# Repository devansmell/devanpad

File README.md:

# devanpad
devanpad is a 4 key macropad with an OLED Display, and QMK firmware.

It serves as an example piece/reference for the hackpad YSWS, since it contains an implementation of every common part.

## Features:
- Open faced ~~sandwich~~ PCB board design.
- OLED Date and Time / Customisable text through python!
- 4 Keys for whatever you want!

## CAD Model:
I quite like the aesthetics of an open PCB, makes me feel like a bond villian; so I am only making a base for the circuit board to sit into. Everything is held together by 4 screws going into the base through the PCB.

Modeled in OnShape.

## PCB
Here's my PCB! It was made in KiCad. The silkscreen is a collection of inside jokes and random images from my computer.

Schematic

PCB

I used Cherry MX1's for the keyswitch footprints. My routing is god awful but if it aint broke dont fix it !!!!

## Firmware Overview

Originally I planned to use QMK firmware, but I switched to CircuitPython + KMK because it made OLED control and development significantly easier.

The firmware:
- Reads key inputs via KMK
- Drives OLED display in real time
- Receives time/date from a Python script over USB serial
- Cycles display modes using a keypress

---

## Host Software (PC Time Sync)

The keyboard receives live system time and date from a Python script running on the computer.

### Setup

```bash
pip install -r host/requirements.txt
python host/main.py
```

This sends:
- Current time every second
- Current date updates
- Optional mode switching commands

## OLED Modes
### Mode 0 — Time
Displays current time from the PC.

### Mode 1 — Date
Displays current date from the PC.

### Mode 2 — Hello Screen
A simple greeting screen.

## BOM:
Here should be everything you need to make this hackpad

- 4x Cherry MX Switches
- 4x DSA Keycaps
- 5x M3x5x4 Heatset inserts
- 2X M2x12mm SHCS Bolts
- 1x 0.91" 128x32 OLED Display
- 1x XIAO RP2040
- 1x Base (3D Printed)
- 1x Soldering Iron (I don't own one)

### Build Notes
Designed as a simple open PCB macropad
Firmware is fully CircuitPython-based (no compilation required)
OLED is driven over I2C
PC <----> device communication uses USB serial

## Extra Stuff
Built this over a whole day and somehow didn’t realize it didn’t count toward my hackatime hours #killme 

_Theoretically_ this will work

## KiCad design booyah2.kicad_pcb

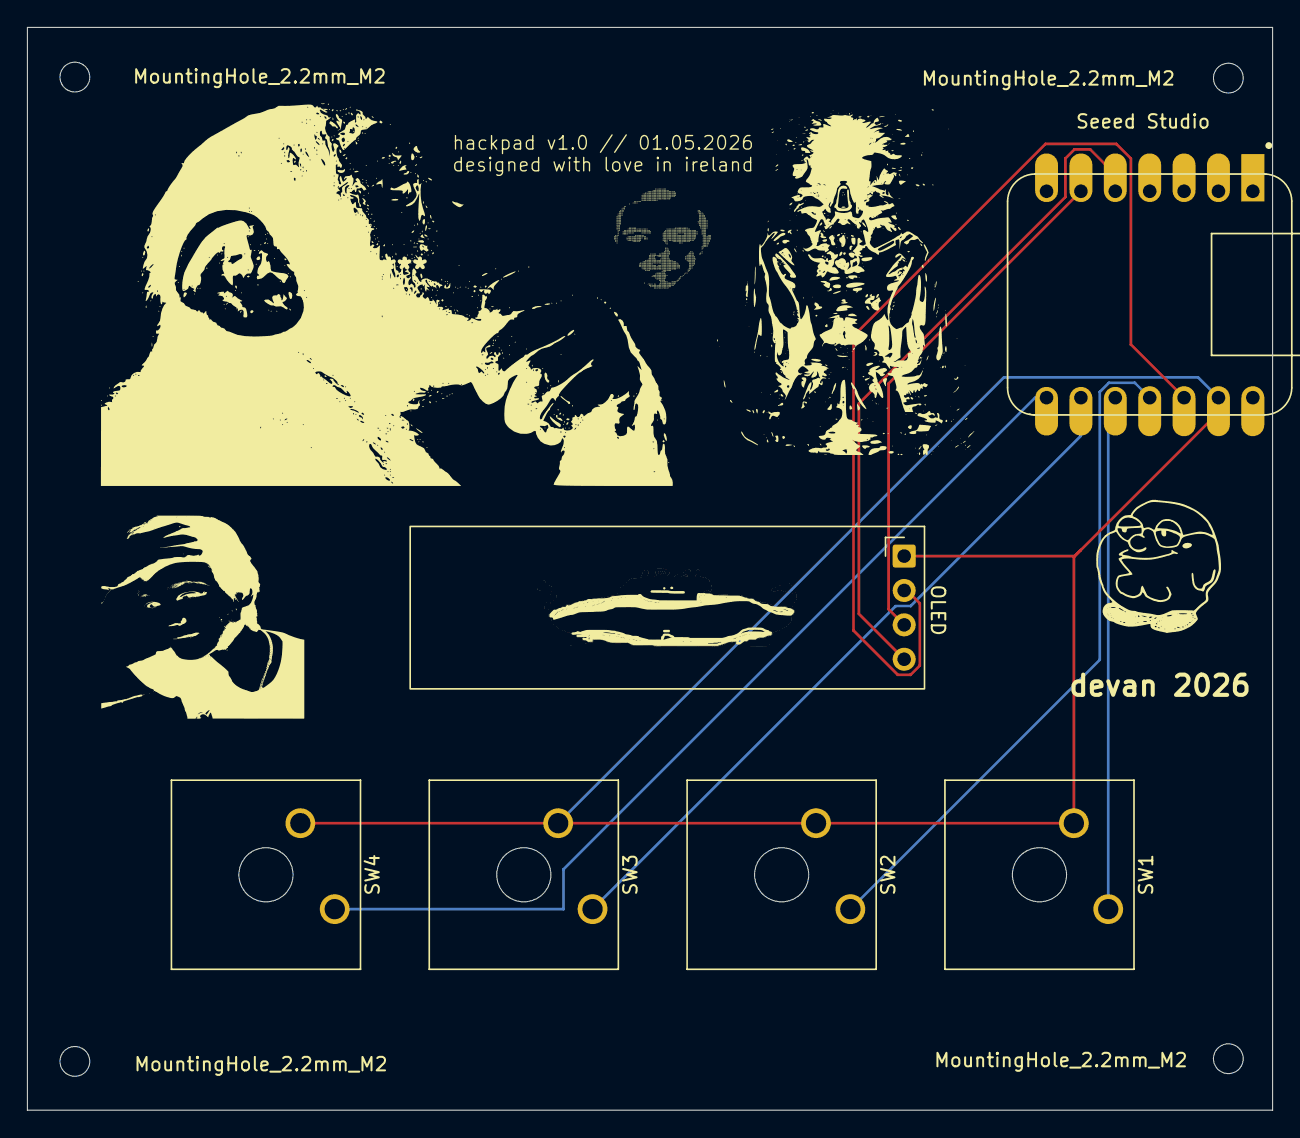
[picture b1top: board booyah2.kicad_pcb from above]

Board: 2 copper layers, 92.0 x 80.0 mm, 7 parts (0 on the bottom side), 8 nets.

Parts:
OLED: ER_OLEDM0.91_1x-I2C
SW1, SW2, SW3, SW4: SW_Push; SW_Cherry_MX_1.00u_Plate
U1: MOUDLE-SEEEDUINO-XIAO; XIAO-Generic-Hybrid-14P-2.54-21X17.8MM
devan 2026: LOGO

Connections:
GND: OLED.1 (GND), SW1.2, SW2.2, SW3.2, SW4.2, U1.13 (GND)
unnamed: OLED.2 (VCC), U1.12 (3V3)
unnamed: SW1.1, U1.10 (PA5_A9_D9_MISO)
unnamed: SW2.1, U1.11 (PA6_A10_D10_MOSI)
unnamed: SW3.1, U1.9 (PA7_A8_D8_SCK)
unnamed: OLED.4 (SDA), U1.5 (PA8_A4_D4_SDA)
unnamed: OLED.3 (SCL), U1.6 (PA9_A5_D5_SCL)
unnamed: SW4.1, U1.8 (PB09_A7_D7_RX)

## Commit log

2026-06-01 i cant compile it lol
